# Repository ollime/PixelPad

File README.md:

# PixelPad

A macropad with 12 keys + 1 rotary encoder.

## Specifications

### BOM

- 1x Seeed XIAO RP2040 Microcontroller x1
- 13x Through-hole 1N4148 Diodes
- 12x Cherry MX-Style Switches
- 1x EC11 Rotary encoders
- 12x Blank DSA keycaps
- 1x 3D printed case
- 5x M3x5mx4mm heatset inserts
- 4x M3x16mm screws

### Other

- QMK Firmware

#### Key mappings

     ┌───┬───┬───┬───┐
     │ 7 │ 8 │ 9 │Ent│
     ├───┼───┼───┼───┤
     │ 4 │ 5 │ 6 │ 0 │
     ├───┼───┼───┼───┤
     │ 1 │ 2 │ 3 │Del│
     └───┴───┴───┴───┘

     Rotary encoder left: scroll up
     Rotary encoder right: scroll down

## Schematic

## PCB

## CAD Model

Key caps not shown

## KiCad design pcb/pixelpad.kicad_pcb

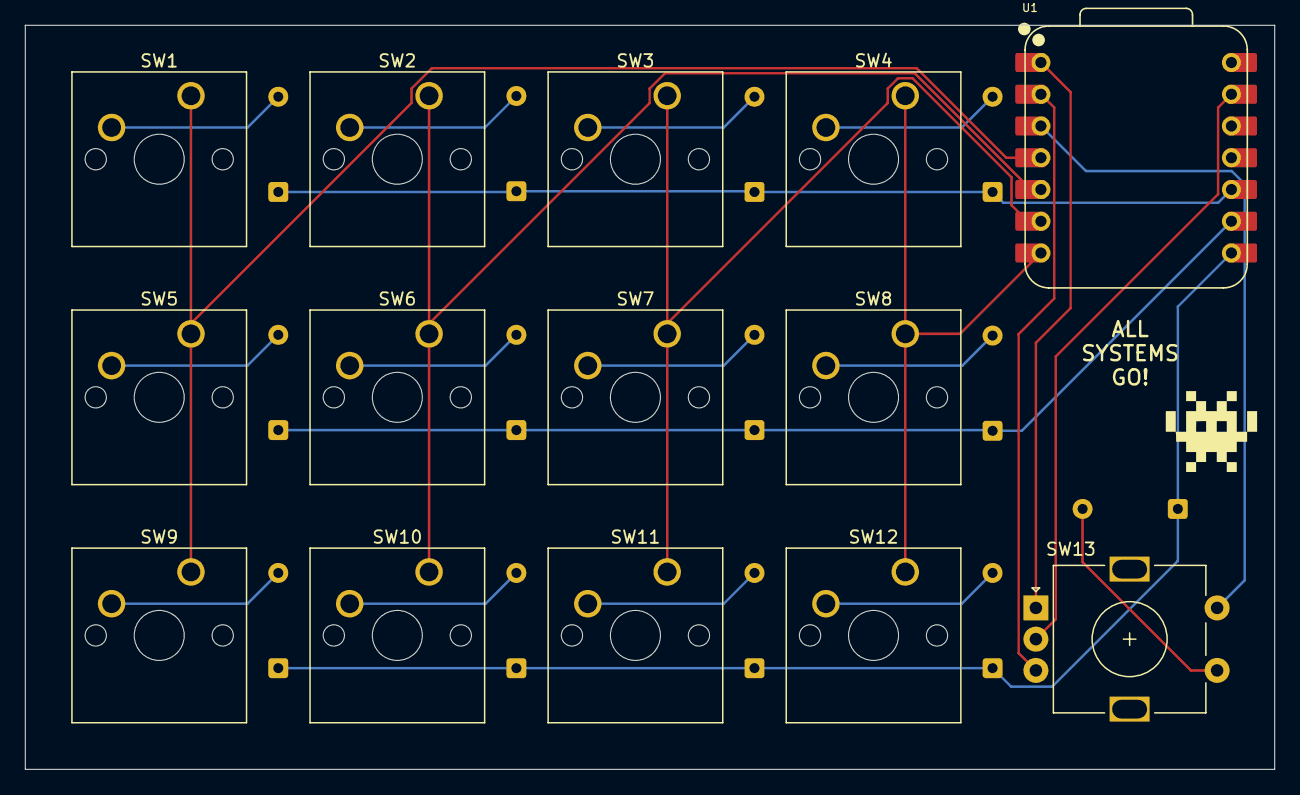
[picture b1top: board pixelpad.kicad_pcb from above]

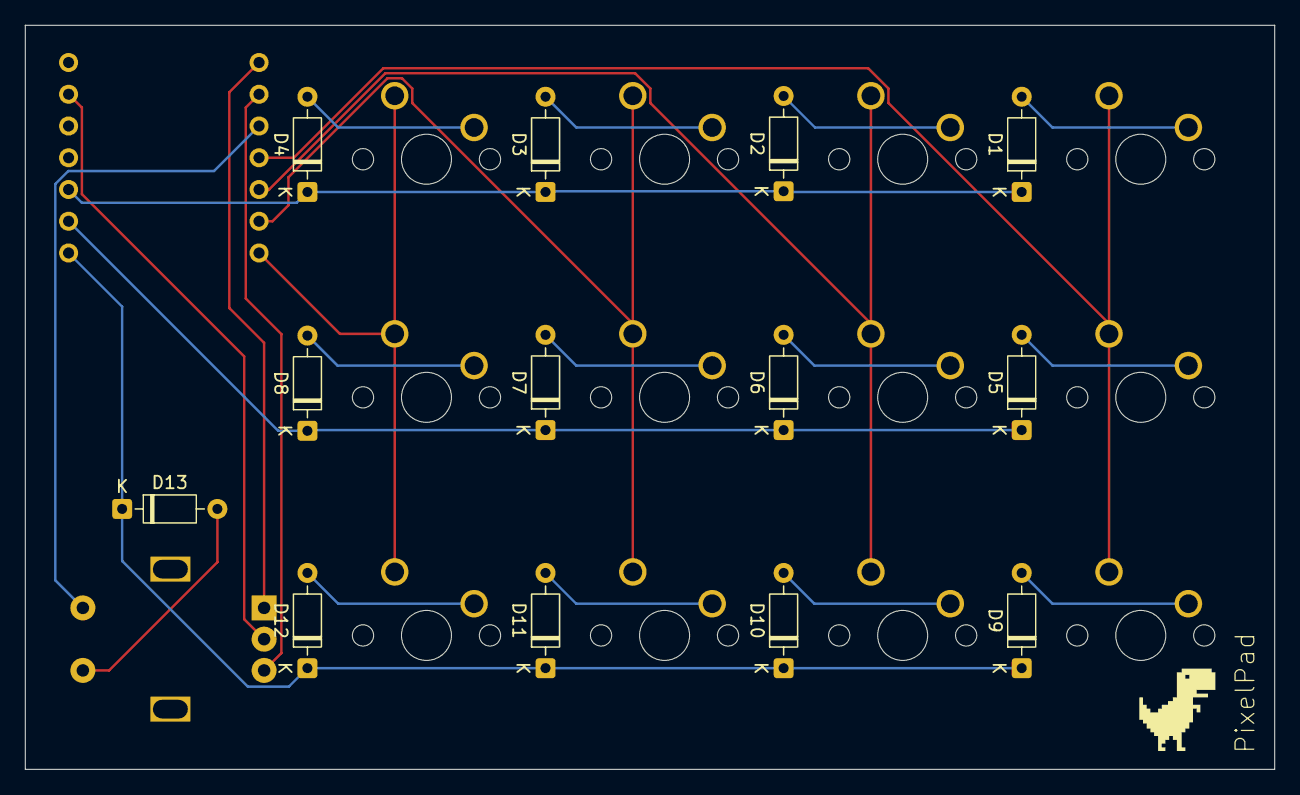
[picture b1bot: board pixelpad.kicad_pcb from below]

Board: 2 copper layers, 100.0 x 59.5 mm, 27 parts (13 on the bottom side), 24 nets.

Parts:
D1, D2, D3, D4, D5, D6, D7, D8, D9, D10, D11, D12, D13: 1N4148WT; D_DO-35_SOD27_P7.62mm_Horizontal
SW1, SW2, SW3, SW4, SW5, SW6, SW7, SW8, SW9, SW10, SW11, SW12: SW_Push; SW_Cherry_MX_1.00u_PCB
SW13: RotaryEncoder_Switch; RotaryEncoder_Alps_EC11E-Switch_Vertical_H20mm
U1: XIAO-RP2040-DIP

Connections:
COL0: SW1.1, SW5.1, SW9.1, U1.4 (GPIO29/ADC3/A3)
COL1: SW2.1, SW6.1, SW10.1, U1.5 (GPIO6/SDA)
COL2: SW3.1, SW7.1, SW11.1, U1.6 (GPIO7/SCL)
COL3: SW4.1, SW8.1, SW12.1, U1.7 (GPIO0/TX)
ENC_A: SW13.A, U1.1 (GPIO26/ADC0/A0)
ENC_B: SW13.B, U1.2 (GPIO27/ADC1/A1)
ENC_SWB: SW13.S2, U1.3 (GPIO28/ADC2/A2)
GND: SW13.C, U1.13 (GND)
unnamed: D1.2 (A), SW1.2
unnamed: D2.2 (A), SW2.2
unnamed: D3.2 (A), SW3.2
unnamed: D4.2 (A), SW4.2
unnamed: D5.2 (A), SW5.2
unnamed: D6.2 (A), SW6.2
unnamed: D7.2 (A), SW7.2
unnamed: D8.2 (A), SW8.2
unnamed: D9.2 (A), SW9.2
unnamed: D10.2 (A), SW10.2
unnamed: D11.2 (A), SW11.2
unnamed: D12.2 (A), SW12.2
unnamed: D13.2 (A), SW13.S1
ROW0: D1.1 (K), D2.1 (K), D3.1 (K), D4.1 (K), U1.10 (GPIO4/MISO)
ROW1: D5.1 (K), D6.1 (K), D7.1 (K), D8.1 (K), U1.9 (GPIO2/SCK)
ROW2: D9.1 (K), D10.1 (K), D11.1 (K), D12.1 (K), D13.1 (K), U1.8 (GPIO1/RX)

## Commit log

2025-05-29 designed pcb and partially finished case
2025-05-29 actually added CAD file
2025-05-29 organized file structure, added git ignore
2025-05-29 added sw_push, moved rotary encoder to bottom right, mcu to top right
2025-05-29 added new cad file with rotary encoder model
2025-05-29 added README file draft
2025-05-30 added schematic and pcb files
2025-05-30 started on firmware, finished CAD
2025-05-30 added CAD file to README
2025-05-30 added name to case, working on firmware
2025-05-30 added firmware files
